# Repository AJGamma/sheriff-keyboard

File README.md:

# :gun:Sheriff: A Feature-rich Ergonomic Split Keyboard with Thumb Scroll Wheels

- Double rotary encoder on the thumb cluster mapped to arrow keys by default, ideal for text editing
- Higher keys on the num row, easier to reach
- Similar layout to the more traditional keyboard on notebooks, less mental overload for switching between devices
- Reversible PCB
- Fully generated, including the case, allowing easy modifications
- Configurable case generation
- Both wired and wireless support
- Generated with [Ergogen](https://github.com/ergogen/ergogen)

## :art: Gallery

## :sparkles: Features

### Rotary Encoders
https://github.com/user-attachments/assets/6208423b-0291-43b4-bef7-f6bb31aa5ce3

The core feature of the Sheriff is the easily accessible rotary encoders positioned on the thumb clusters.

#### Encoder behaviors

##### QMK version (`custom_scroll_layers` version)

| Behavior        | Key Held  | Left Counter-clockwise          | Left Clockwise                  | Right Counter-clockwise         | Right Clockwise                 |
|-----------------|-----------|---------------------------------|---------------------------------|---------------------------------|---------------------------------|
| Arrow key       | None      | Left                            | Right                           | Down                            | Up                              |
| Deletion        | Backspace | Backspace                       | Delete                          | Backspace                       | Delete                          |
| Mouse wheel     | Esc       | Volume-down                     | Volume-up                       | Mouse wheel down                | Mouse wheel up                  |
| Repeating       | Space     | Left                            | Right                           | Repeat last key                 | Repeat last key's alternative   |
| Mouse emulation | V         | Mouse left                      | Mouse right                     | Mouse down                      | Mouse up                        |
| Vim motion      | W         | b                               | w                               | }                               | {                               |
| Vim motion      | E         | ge                              | e                               | Down                            | Up                              |
| Vim undo/redo   | U         | u                               | C-r                             | C-r                             | u                               |
| Undo/redo       | Y         | C-z                             | C-y                             | C-y                             | C-z                             |
| Undo/redo       | Z         | C-z                             | S-C-z                           | S-C-z                           | C-z                             |
| Speed up        | 8         | Next activated behavior 8 times | Next activated behavior 8 times | Next activated behavior 8 times | Next activated behavior 8 times |

##### ZMK version

| Behavior        | Key Held  | Left Counter-clockwise | Left Clockwise | Right Counter-clockwise | Right Clockwise               | Description |
|-----------------|-----------|------------------------|----------------|-------------------------|-------------------------------|-------------|
| Arrow key       | None      | Left                   | Right          | Down                    | Up                            |             |
| Deletion        | Backspace | Backspace              | Delete         | Backspace               | Delete                        |             |
| Mouse wheel     | Esc       | Volume-down            | Volume-up      | Mouse wheel down        | Mouse wheel up                | Sym layer   |
| Repeating       | Space     | Left                   | Right          | Repeat last key         | Repeat last key's alternative | Nav layer   |
| Mouse emulation | V         | Mouse left             | Mouse right    | Mouse down              | Mouse up                      | Mouse layer |
| Vim motion      | W         | b                      | w              | }                       | {                             |             |
| Vim motion      | E         | ge                     | e              | Down                    | Up                            |             |
| Speed up        | 8         | Left * 8               | Right * 8      | Down * 8                | Up * 8                        |             |

### Configurable case generation
The case is generated with [ergogen](https://github.com/ergogen/ergogen), and the config file was written with configurability in mind. There are multiple versions of the case, including `flat`, `tented`, `sinfle-sided tented` and `lifted tented`. The parameters are highly adjustable, and customization can easily be done. See the [doc](/docs/case_customization.md) for more information.

### Easier transitions

One of the motivations for this keyboard is to make the transition from a traditional keyboard to an ergonomic one easier. That's why the default layout is mostly the same as a traditional keyboard, with the only difference being the extra keys in thumb clusters. This way, when you switch back to a traditional keyboard and you reach for the thumb cluster mods, they are simply not there, eliminating any chance of pressing the wrong key.

### Higher up num row

The key caps on the num row are higher up, making them easier to reach.

### Both wired and wireless support
The PCB has both trrs jacks and battery pins, allowing for both wired and wireless connections.

Both ZMK(wireless) and QMK(wired) firmware are implemented; however, I've encountered several issues with the ZMK firmware, including:
- Two halves unable to pair(swapping boards did not help, neither did flashing reset firmware, and I'm 90% sure nothing's wrong with the firmware)
- Rotary encoder motions sometimes skipped

It's worth noting that I'm not using the official nice!nano boards, but rather the Pro Micro NRF52840 nice!nano v2 compatible boards, which might be the cause of the issues.

## Firmware
Supports wired usage with [QMK](https://qmk.fm/) firmware. Repository [here](https://github.com/AJGamma/sheriff-qmk-config)

Wireless usage is supported with [ZMK](https://zmk.dev/). Repository [here](https://github.com/AJGamma/sheriff-zmk-config). I couldn't get it to work properly though, detail [here](#both-wired-and-wireless-support).

## Layout

Default layer:

Layer 1:

Layer 2:

Layer 3:

## :bulb: Inspirations

- [This amazing video by Christian Selig](https://www.youtube.com/watch?v=7UXsD7nSfDY) inspired me to build my own keyboard.
- I learned a lot from the [Corax](https://github.com/dnlbauer/corax-keyboard) keyboard, and borrowed some code as well.
- The [Arkenswoop](https://github.com/SuperFola/arkenswoop) keyboard has a similar scroll wheel feature, and I fixed my rotary encoder pin definition after checking its kicad file and the information from [this github repo](https://github.com/rroels/EVQWGD001-Pinout).

## Future work
- [ ] Build guide
- [ ] Screen
- [ ] LEDs
- [ ] More intuitive scroll wheel position and orientation
- [ ] New logo
- [ ] 3D-printed key caps
- [ ] More acquirable scroll wheel

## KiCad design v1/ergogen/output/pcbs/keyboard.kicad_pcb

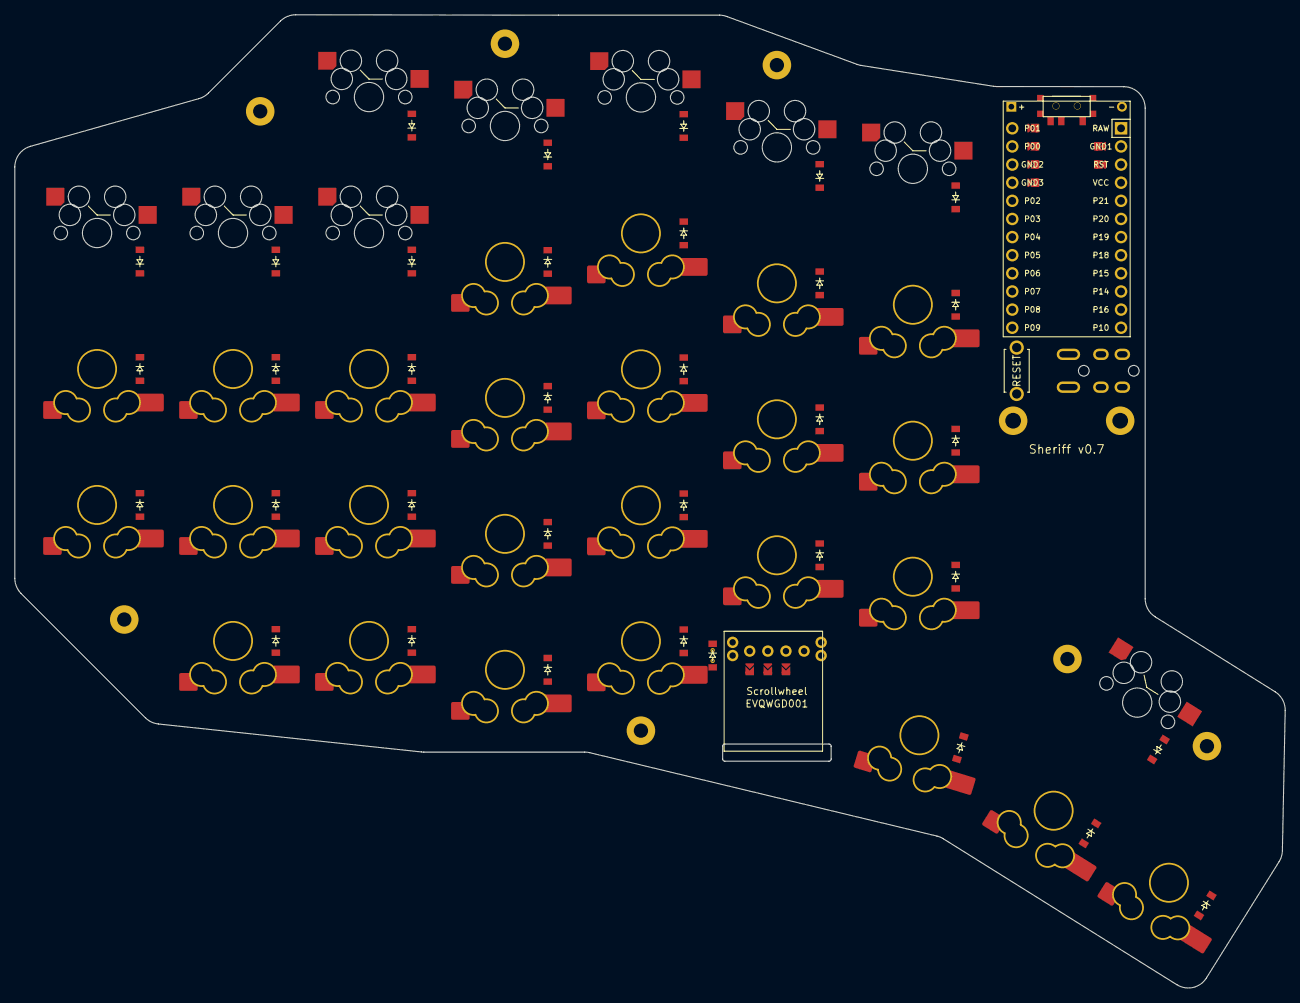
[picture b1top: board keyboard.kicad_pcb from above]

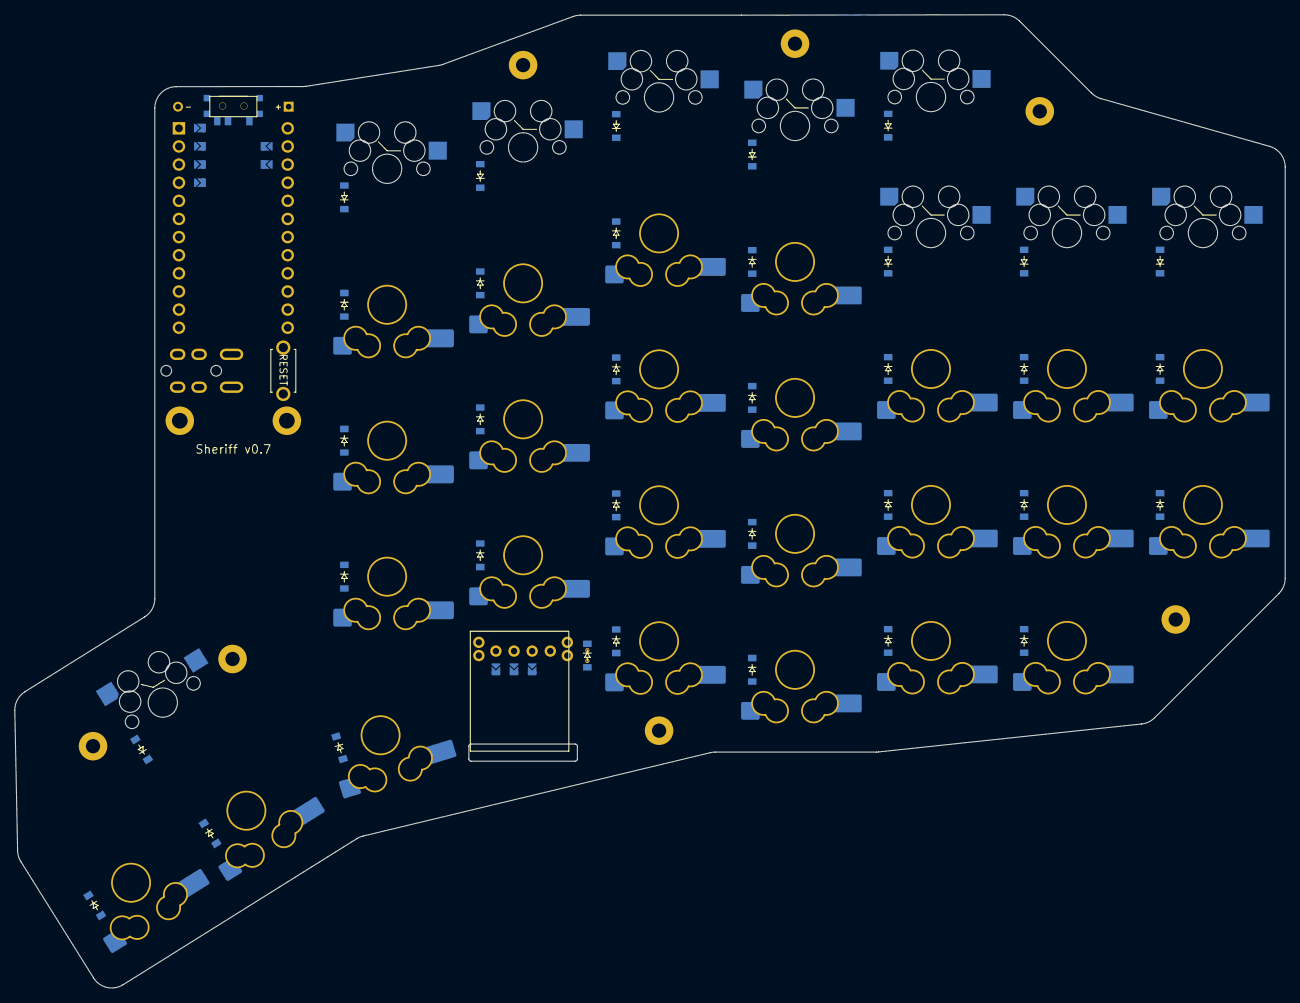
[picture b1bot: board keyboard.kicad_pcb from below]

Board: 2 copper layers, 178.0 x 136.4 mm, 100 parts (68 on the bottom side), 63 nets, no tracks yet.

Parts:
D1, D2, D3, D4, D5, D6, D7, D8, D9, D10, D11, D12, D13, D14, D15, D16, D17, D18, D19, D20, D21, D22, D23, D24, D25, D26, D27, D28, D29, D30, D31, D32, D33, D34: diode_tht_sod123
D35: ComboDiode
J1, J2, J3, J4, J5, J6, J7, J8, J9, J10, J11, J12, J13, J14, J15, J16, J17, J18: Jumper
MCU1: ProMicro
S1, S2, S3, S4, S5, S6, S7, S8, S9, S10, S11, S12, S13, S14, S15, S16, S17, S18, S19, S20, S21, S22, S23, S24, S25: switch_gateron_ks27_ks33
S26, S27, S28, S29, S30, S31, S32, S33, S34: switch_mx
T1: SPDT_C128955
TRRS1: trrs_pj320a (reversible, symmetric)
_1: ResetSW
_2, _3, _4, _5, _6, _7, _8, _9, _10: Hole

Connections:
ENCA: J1.2, J4.2, MCU1.5
ENCB: J2.2, J5.2, MCU1.17
ENCB_GND: J2.1, J6.1
GND: J3.2, J6.2, J7.2, J10.2, J14.2, J18.2, TRRS1.4, _1.2
GND_ENCB: J3.1, J5.1
GND_RST: J10.1, J17.1, MCU1.15
GND_VCC: J13.1, MCU1.16
GND_serial: J7.1, J15.1, MCU1.2
P1_RAW: J16.1, MCU1.13
RAW: J9.2, J16.2, T1.2
RAW_P1: J9.1, MCU1.1
RST: J11.2, J17.2, _1.1
RST_GND: J11.1, J18.1, MCU1.3
VCC: J12.2, J13.2, TRRS1.2
VCC_GND: J12.1, MCU1.4
col0: MCU1.6, S1.1, S2.1, S24.1, S25.1, S26.2
col1: MCU1.7, S3.1, S4.1, S5.1, S27.2, S34.2
col2: MCU1.8, S6.1, S7.1, S8.1, S28.2, S29.2
col3: MCU1.9, S9.1, S10.1, S11.1, S12.1, S30.2
col4: MCU1.10, S13.1, S14.1, S15.1, S16.1, S31.2
col5: MCU1.11, S17.1, S18.1, S19.1, S32.2
col6: MCU1.12, S20.1, S21.1, S22.1, S23.1, S33.2
home_high: D34.2, S34.1
home_low: D24.2, S24.2
index_bottom: D17.2, S17.2
index_home: D18.2, S18.2
index_num: D32.2, S32.1
index_top: D19.2, S19.2
inner_bottom: D20.2, S20.2
inner_home: D21.2, S21.2
inner_low: D23.2, S23.2
inner_num: D33.2, S33.1
inner_top: D22.2, S22.2
middle_bottom: D14.2, S14.2
middle_home: D15.2, S15.2
middle_mod: D13.2, S13.2
middle_num: D31.2, S31.1
middle_top: D16.2, S16.2
outer1_bottom: D4.2, S4.2
outer1_home: D5.2, S5.2
outer1_mod: D3.2, S3.2
outer1_top: D27.2, S27.1
outer2_bottom: D1.2, S1.2
outer2_home: D2.2, S2.2
outer2_top: D26.2, S26.1
outer_low: D25.2, S25.2
pinky_bottom: D7.2, S7.2
pinky_home: D8.2, S8.2
pinky_mod: D6.2, S6.2
pinky_num: D29.2, S29.1
pinky_top: D28.2, S28.1
ring_bottom: D10.2, S10.2
ring_home: D11.2, S11.2
ring_mod: D9.2, S9.2
ring_num: D30.2, S30.1
ring_top: D12.2, S12.2
row0: D26.1, D29.1, D30.1, D31.1, D32.1, D33.1, D34.1, MCU1.20
row1: D2.1, D12.1, D16.1, D19.1, D22.1, D27.1, D28.1, MCU1.21
row2: D1.1, D5.1, D8.1, D11.1, D15.1, D18.1, D21.1, MCU1.22
row3: D4.1, D7.1, D10.1, D14.1, D17.1, D20.1, D25.1, MCU1.23
row4: D3.1, D6.1, D9.1, D13.1, D23.1, D24.1, D35.1, MCU1.24
serial: J8.2, J15.2, TRRS1.3
serial_GND: J8.1, J14.1, MCU1.14

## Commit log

2024-10-11 basic layout
    new file: README.md
    modified: ergogen/config.yaml
2024-10-14 altered positions, finished outline
2024-10-20 nicenano version
2024-10-23 pcbs and cases
2024-10-26 routed pcb
2024-10-26 added teardrops
2024-10-26 jumper sides
2024-10-27 first release 0.7
2024-10-28 lifted tenting mounts
2024-11-01 gitignore
2024-11-02 switchplate thickness update
2024-11-02 readme 60%
2024-11-04 fixed rotor pinout, updated jumper side
2024-11-13 updated readme; fixed switchplate
2024-11-13 Create LICENSE
2024-11-13 fixed switchplate
2024-11-14 updated switchplate model
2024-11-17 margin
2024-11-17 updated build guide; updated scroll wheel behavior table
2024-11-17 Update README.md, added demo video
2024-11-18 Updated build_guide.md, added missing part
2024-11-20 completed build guide and case customization doc
2024-11-21 better wall height and usb cutout position
2024-12-12 refactored: 2 versions
2024-12-12 removed output
